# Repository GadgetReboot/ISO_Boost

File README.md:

# ISO_Boost
Isolated 5v-27v boost converter

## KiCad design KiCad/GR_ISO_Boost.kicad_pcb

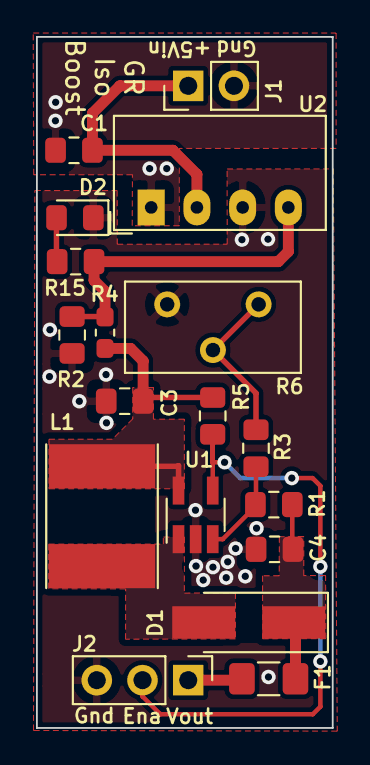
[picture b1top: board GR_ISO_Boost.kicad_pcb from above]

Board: 2 copper layers, 16.4 x 38.4 mm, 18 parts (0 on the bottom side), 12 nets.

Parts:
C1, C3, C4: 1uF; C_0805_2012Metric_Pad1.15x1.40mm_HandSolder
D1: SS16; D_SMA_Handsoldering
D2: LED; LED_0805_2012Metric_Pad1.15x1.40mm_HandSolder
F1: PTC; Fuse_1206_3216Metric_Pad1.42x1.75mm_HandSolder
J1: Conn_01x02; PinHeader_1x02_P2.54mm_Vertical
J2: Conn_01x03; PinHeader_1x03_P2.54mm_Vertical
L1: 22uH; L_Taiyo-Yuden_NR-60xx_HandSoldering
R1: 33K; R_0805_2012Metric_Pad1.15x1.40mm_HandSolder
R2: 390r; R_0805_2012Metric_Pad1.15x1.40mm_HandSolder
R3: 1K5; R_0805_2012Metric_Pad1.15x1.40mm_HandSolder
R4: 0r; R_0603_1608Metric_Pad1.05x0.95mm_HandSolder
R5: 100K; R_0805_2012Metric_Pad1.15x1.40mm_HandSolder
R6: 10K; Potentiometer_Bourns_3386X_Horizontal
R15: 1K; R_0805_2012Metric_Pad1.15x1.40mm_HandSolder
U1: AP3012; SOT-23-5_HandSoldering
U2: B0505S; Converter_DCDC_muRata_CRE1xxxxxxSC_THT

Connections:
/+5V_ISO: R2.1, R4.2, R15.1, U2.4
/+5Vin: C1.1, J1.1, U2.2
/Ena: J2.2, R5.2, U1.4
/Gnd_In: C1.2, J1.2, U2.1
GNDREF: C3.2, C4.2, D2.1, J2.3, R2.2, R6.3, U1.2, U2.3
unnamed: C3.1, L1.1, R4.1, R5.1, U1.5
unnamed: C4.1, D1.1, F1.2, R1.2
unnamed: D1.2, L1.2, U1.1
unnamed: D2.2, R15.2
unnamed: F1.1, J2.1
unnamed: R1.1, R3.2, U1.3
unnamed: R3.1, R6.1, R6.2
